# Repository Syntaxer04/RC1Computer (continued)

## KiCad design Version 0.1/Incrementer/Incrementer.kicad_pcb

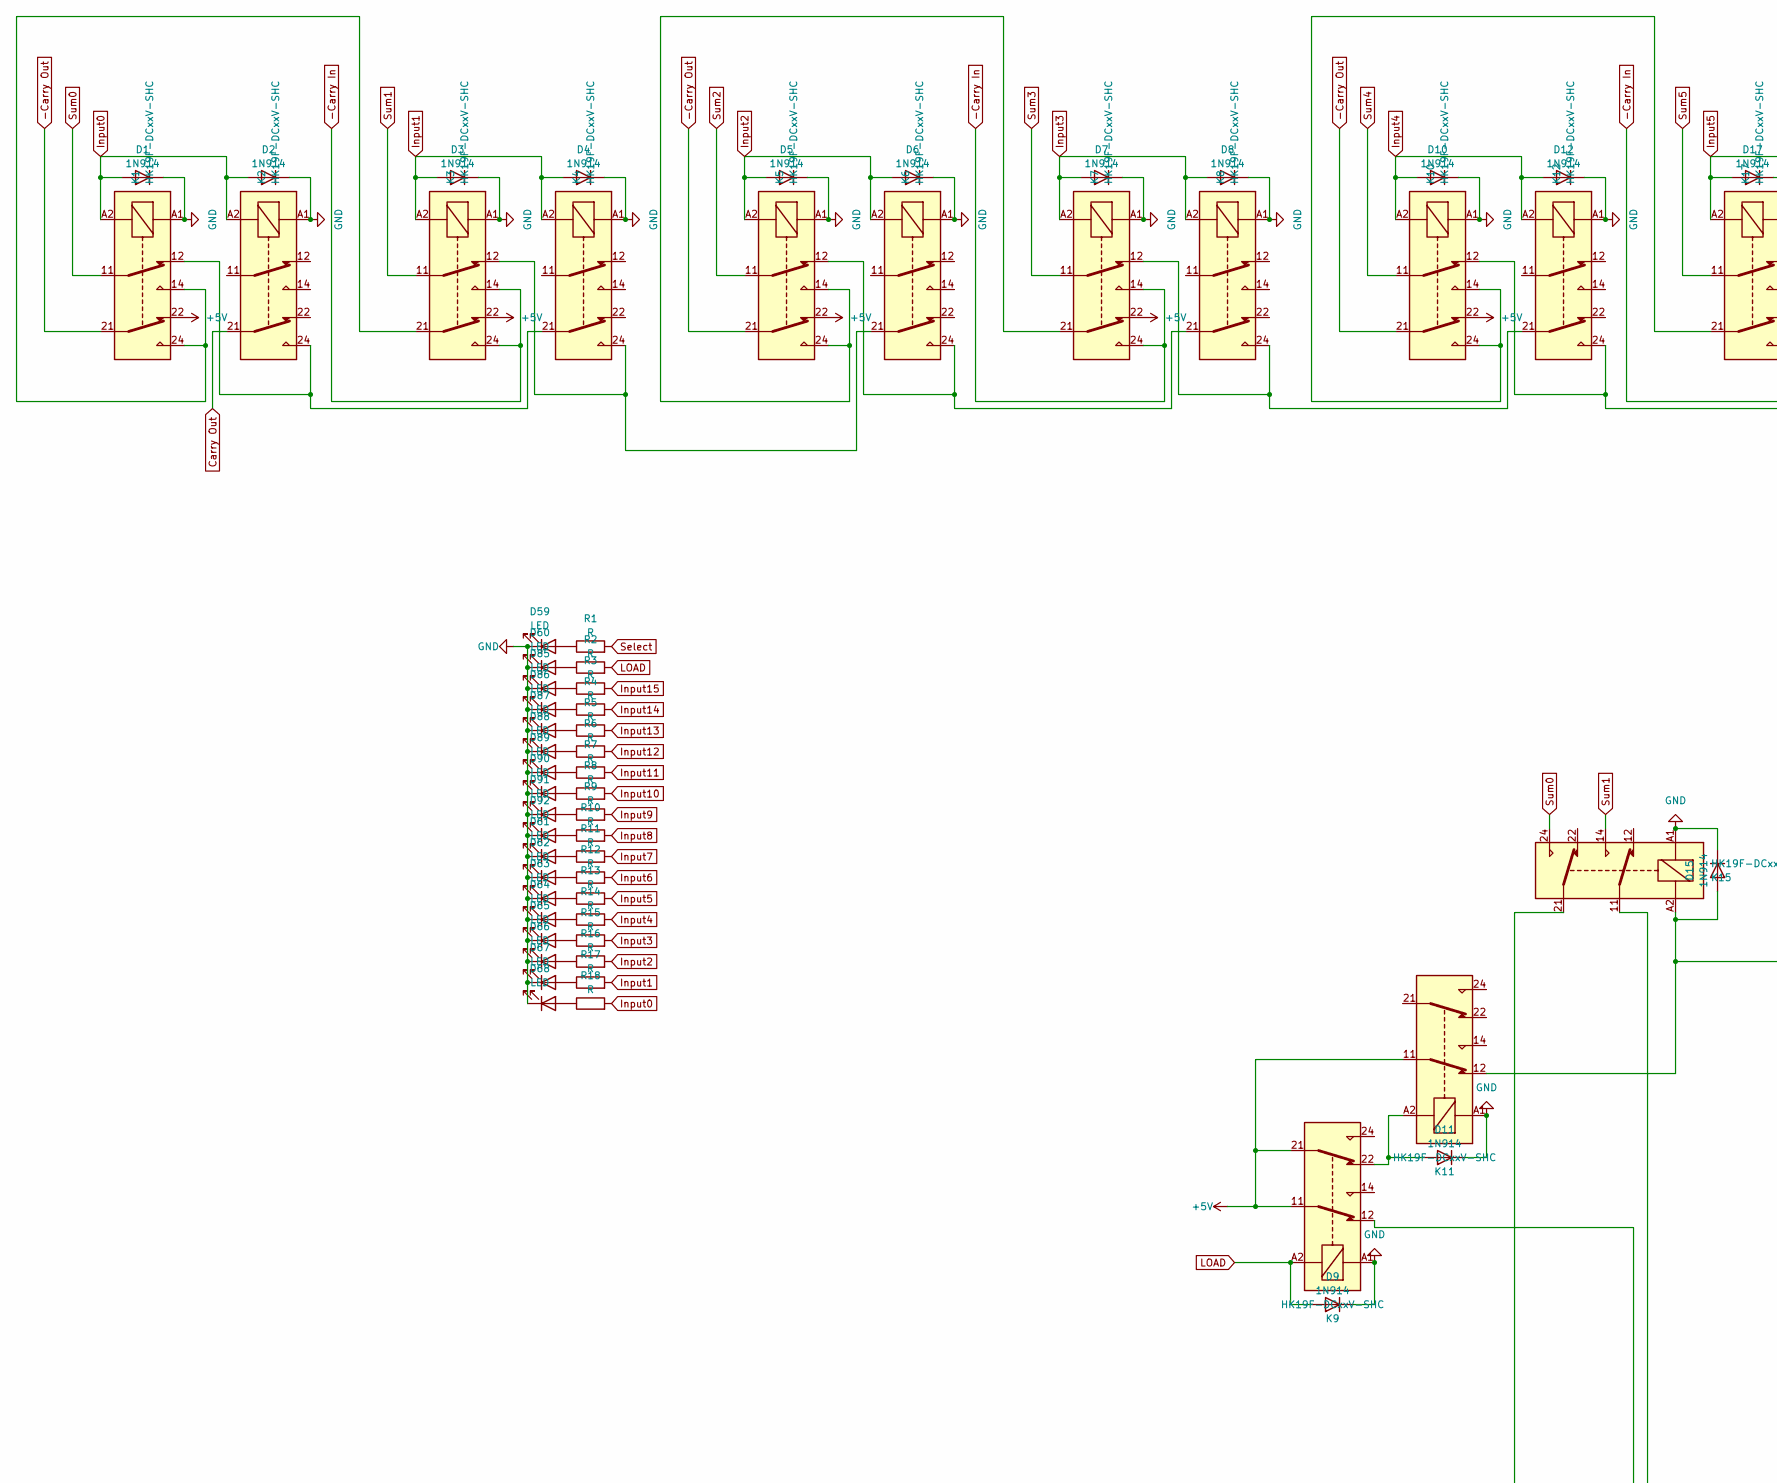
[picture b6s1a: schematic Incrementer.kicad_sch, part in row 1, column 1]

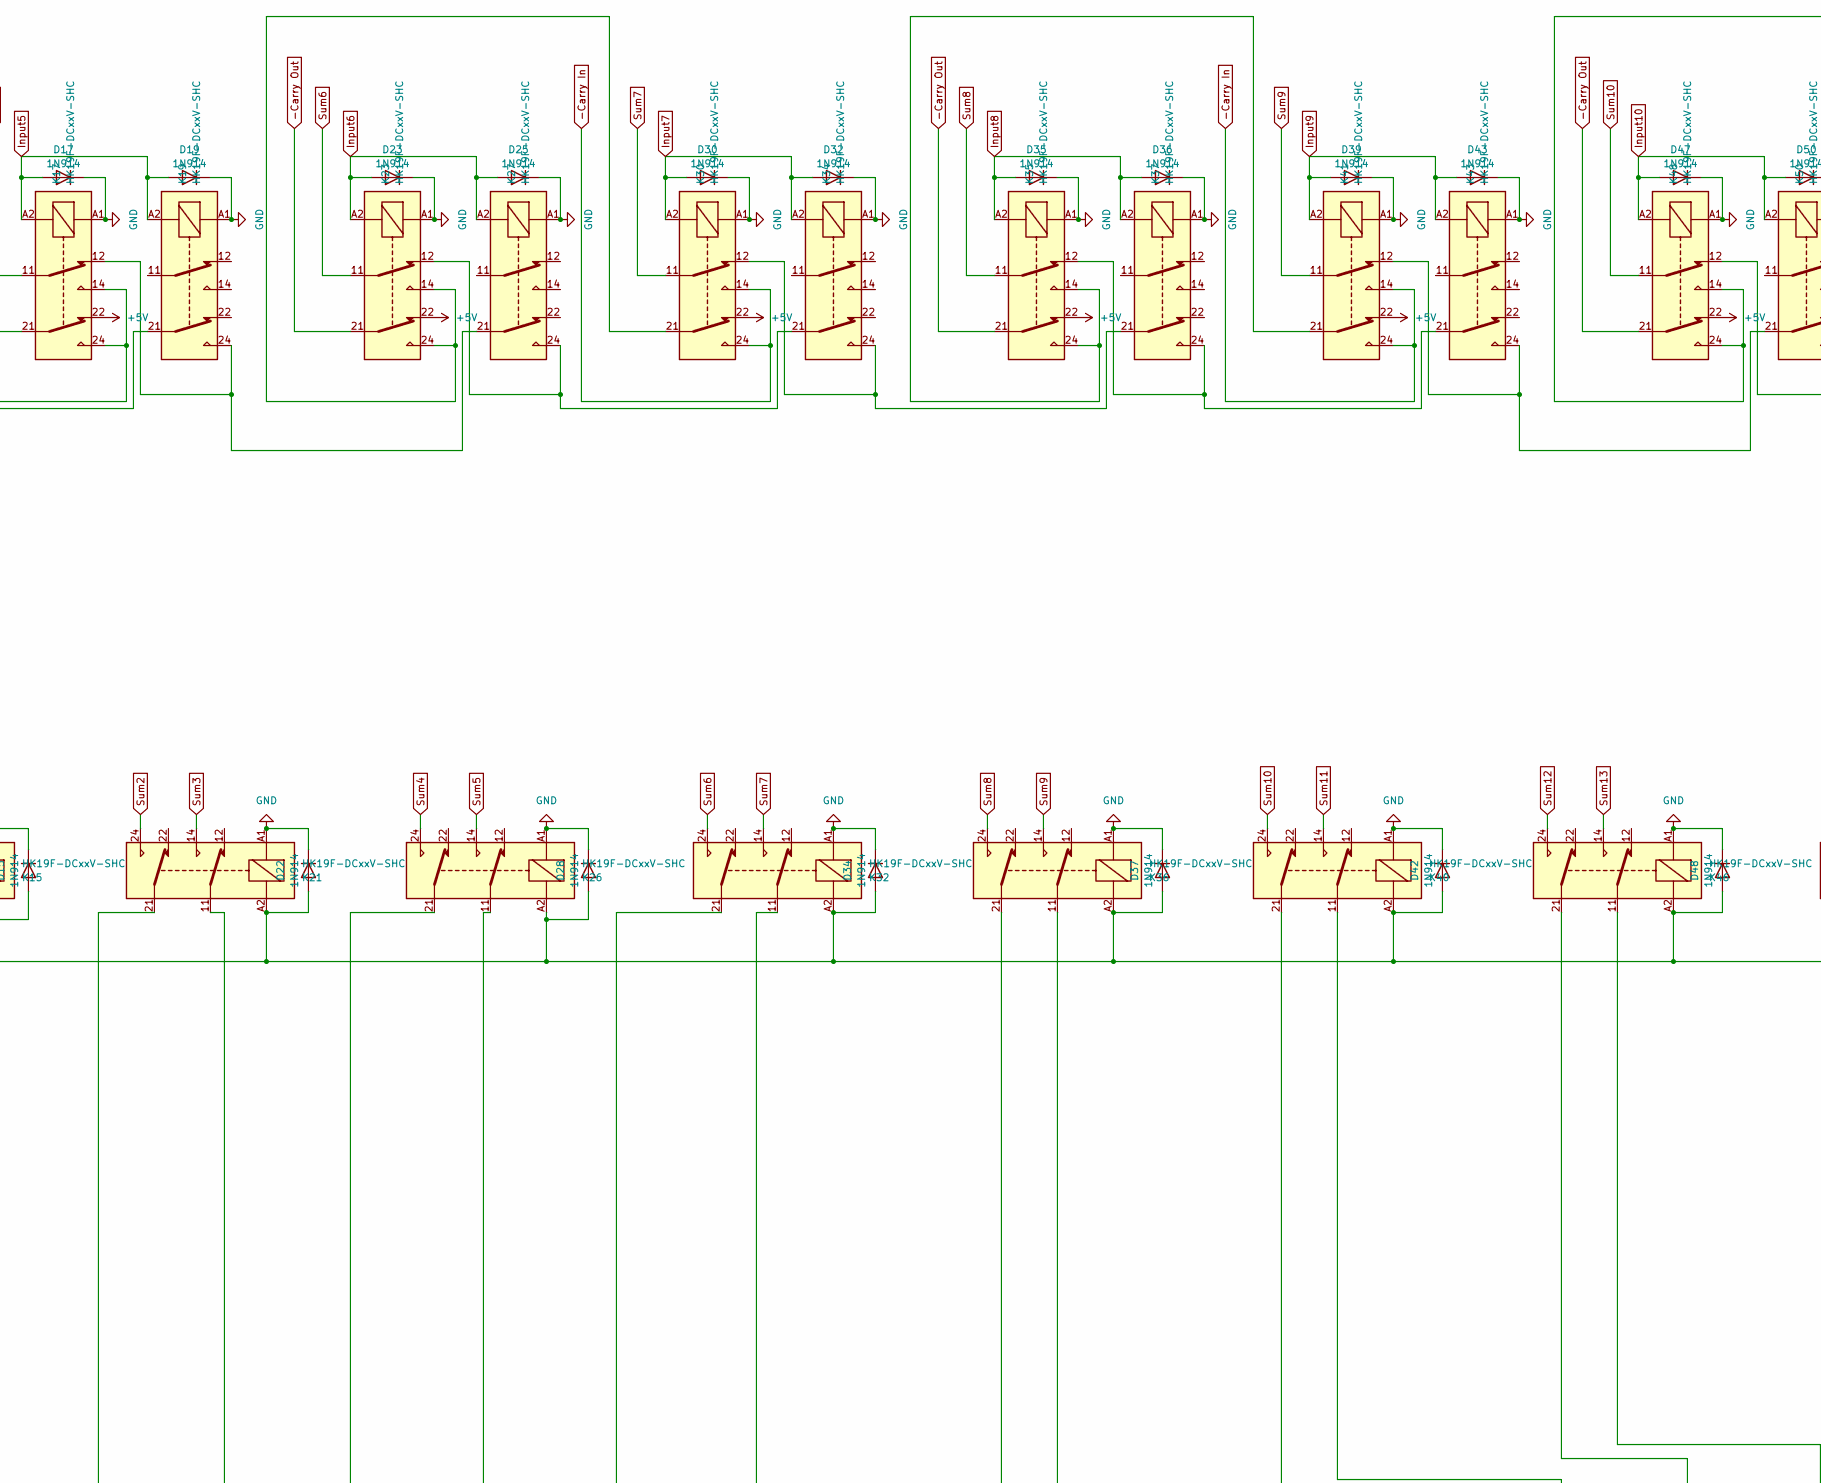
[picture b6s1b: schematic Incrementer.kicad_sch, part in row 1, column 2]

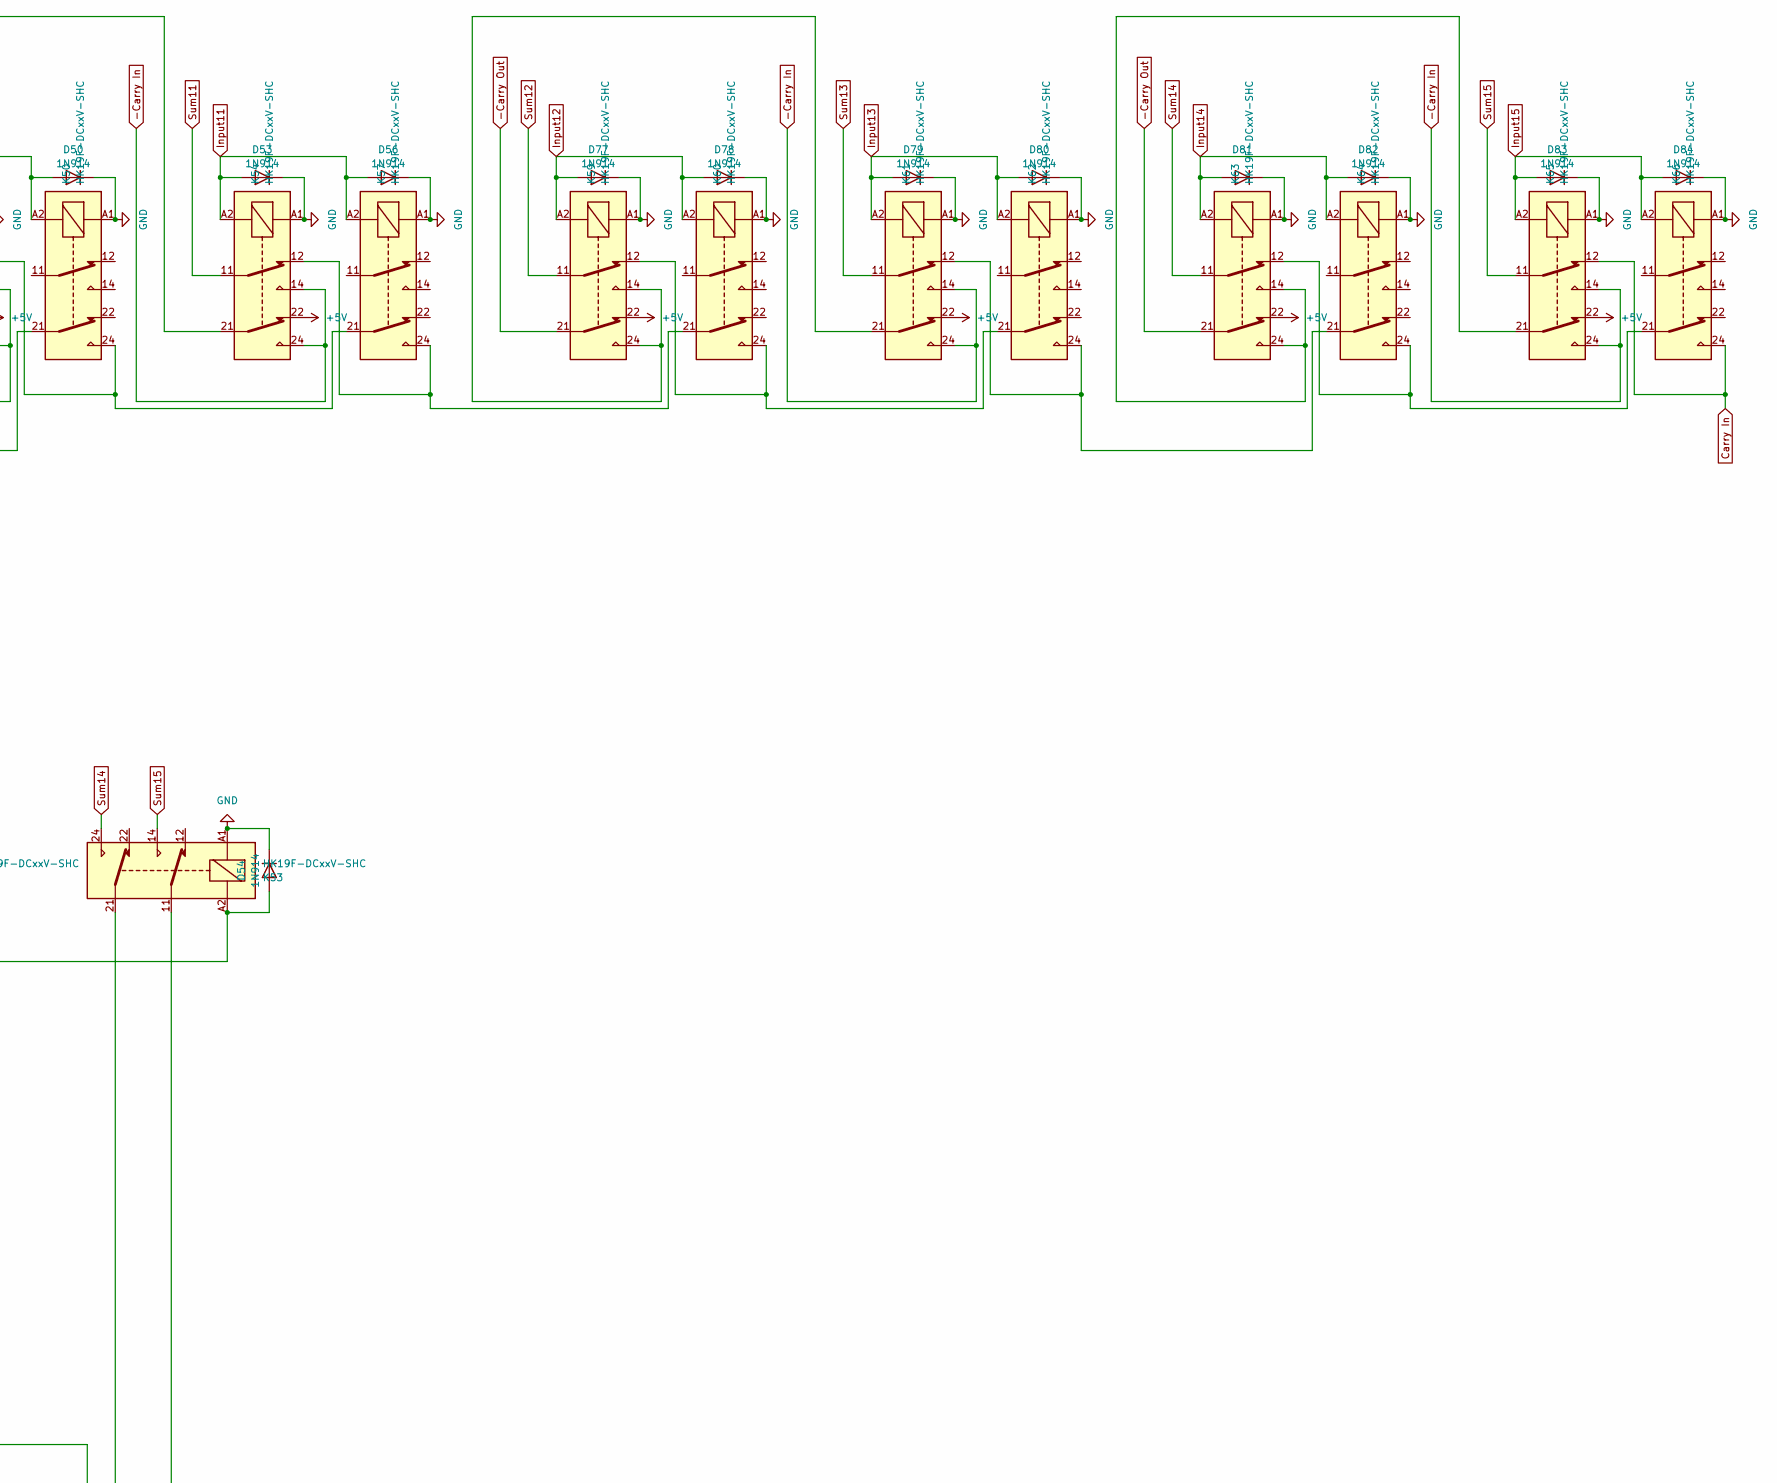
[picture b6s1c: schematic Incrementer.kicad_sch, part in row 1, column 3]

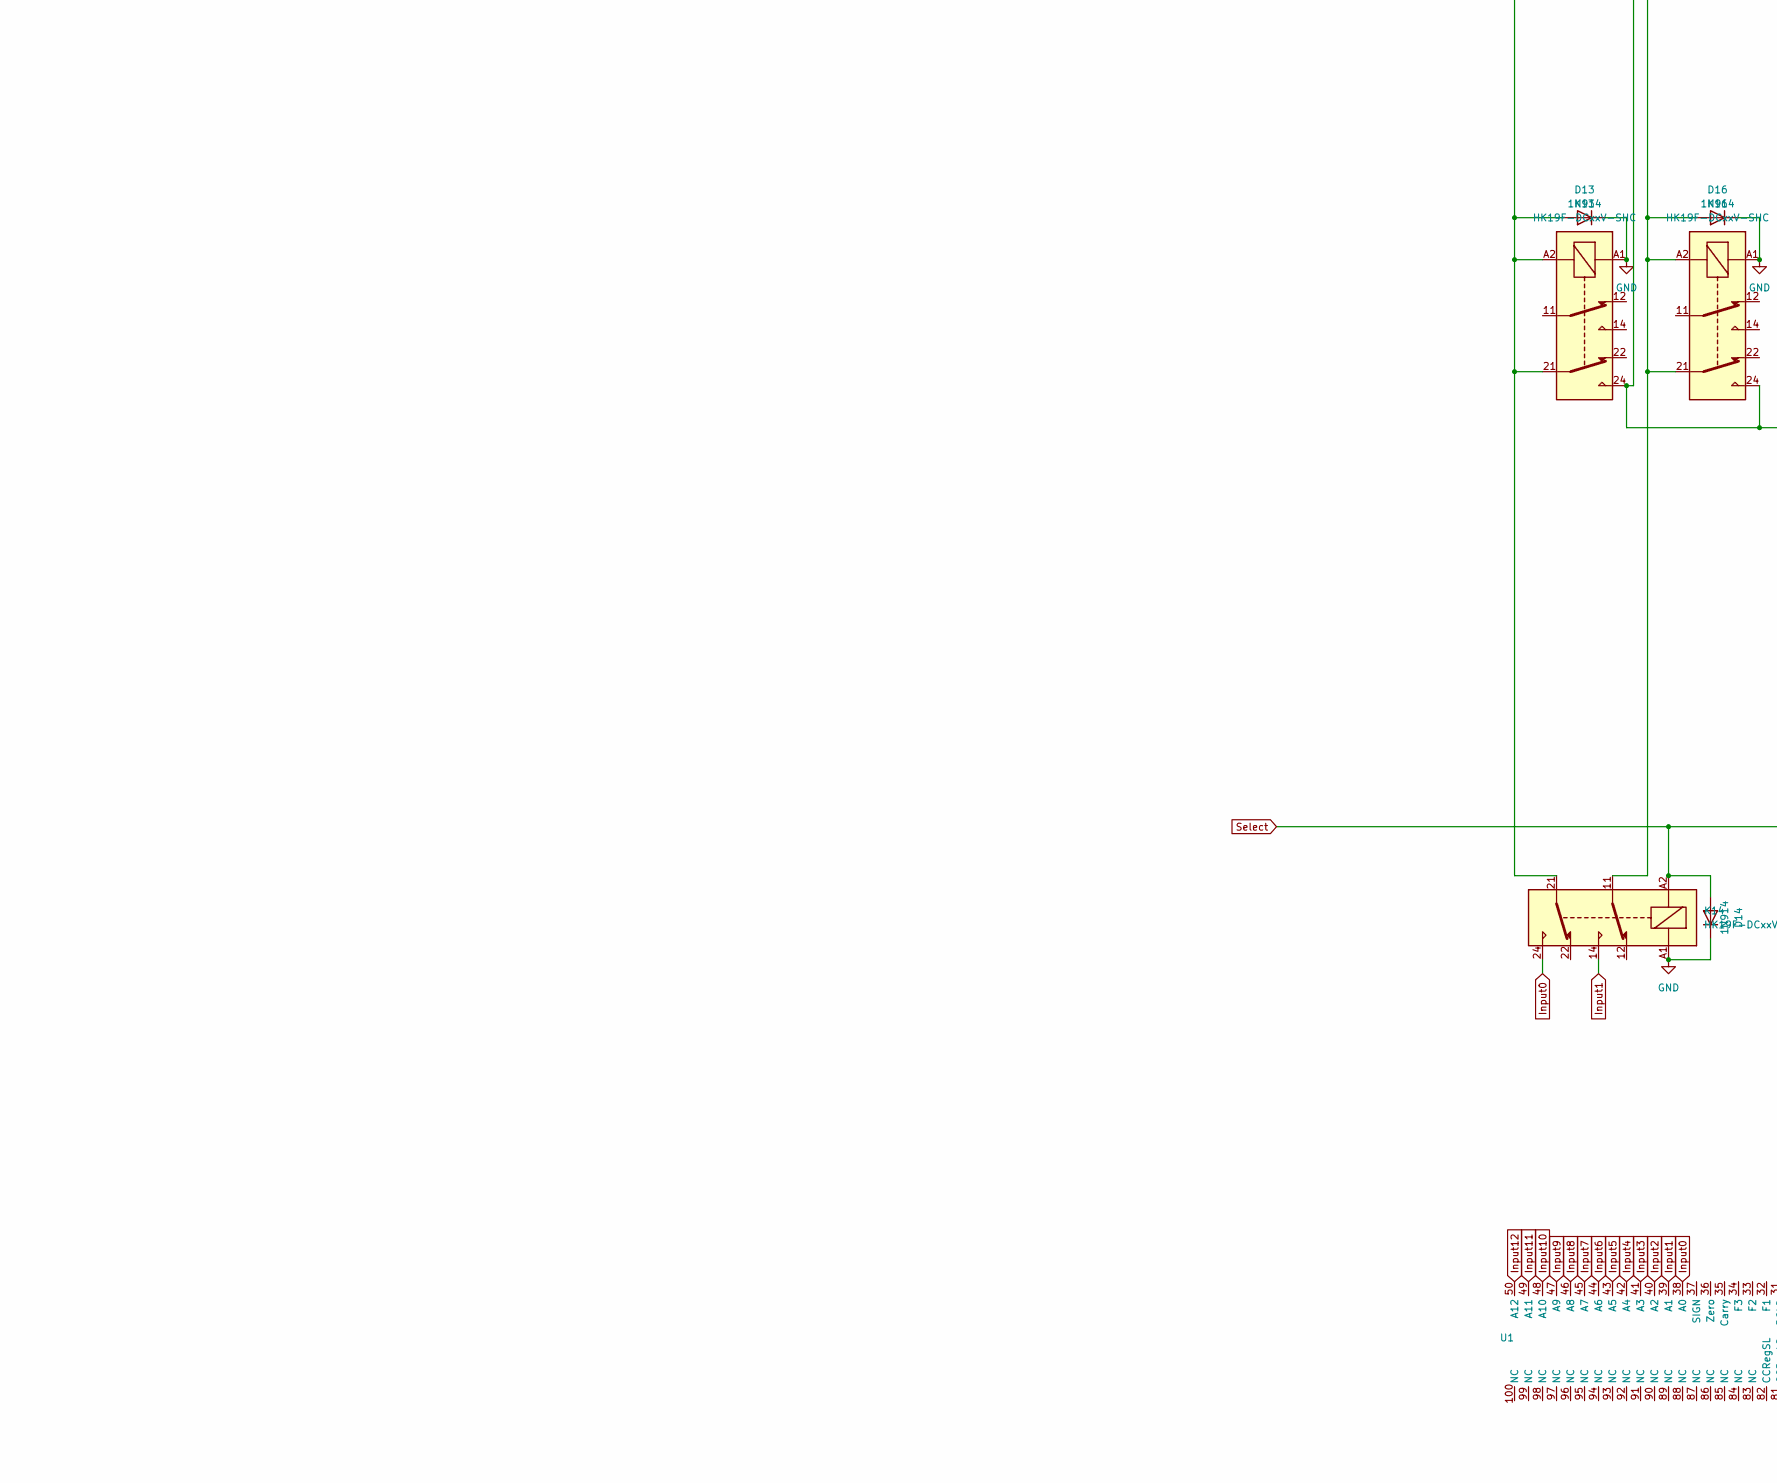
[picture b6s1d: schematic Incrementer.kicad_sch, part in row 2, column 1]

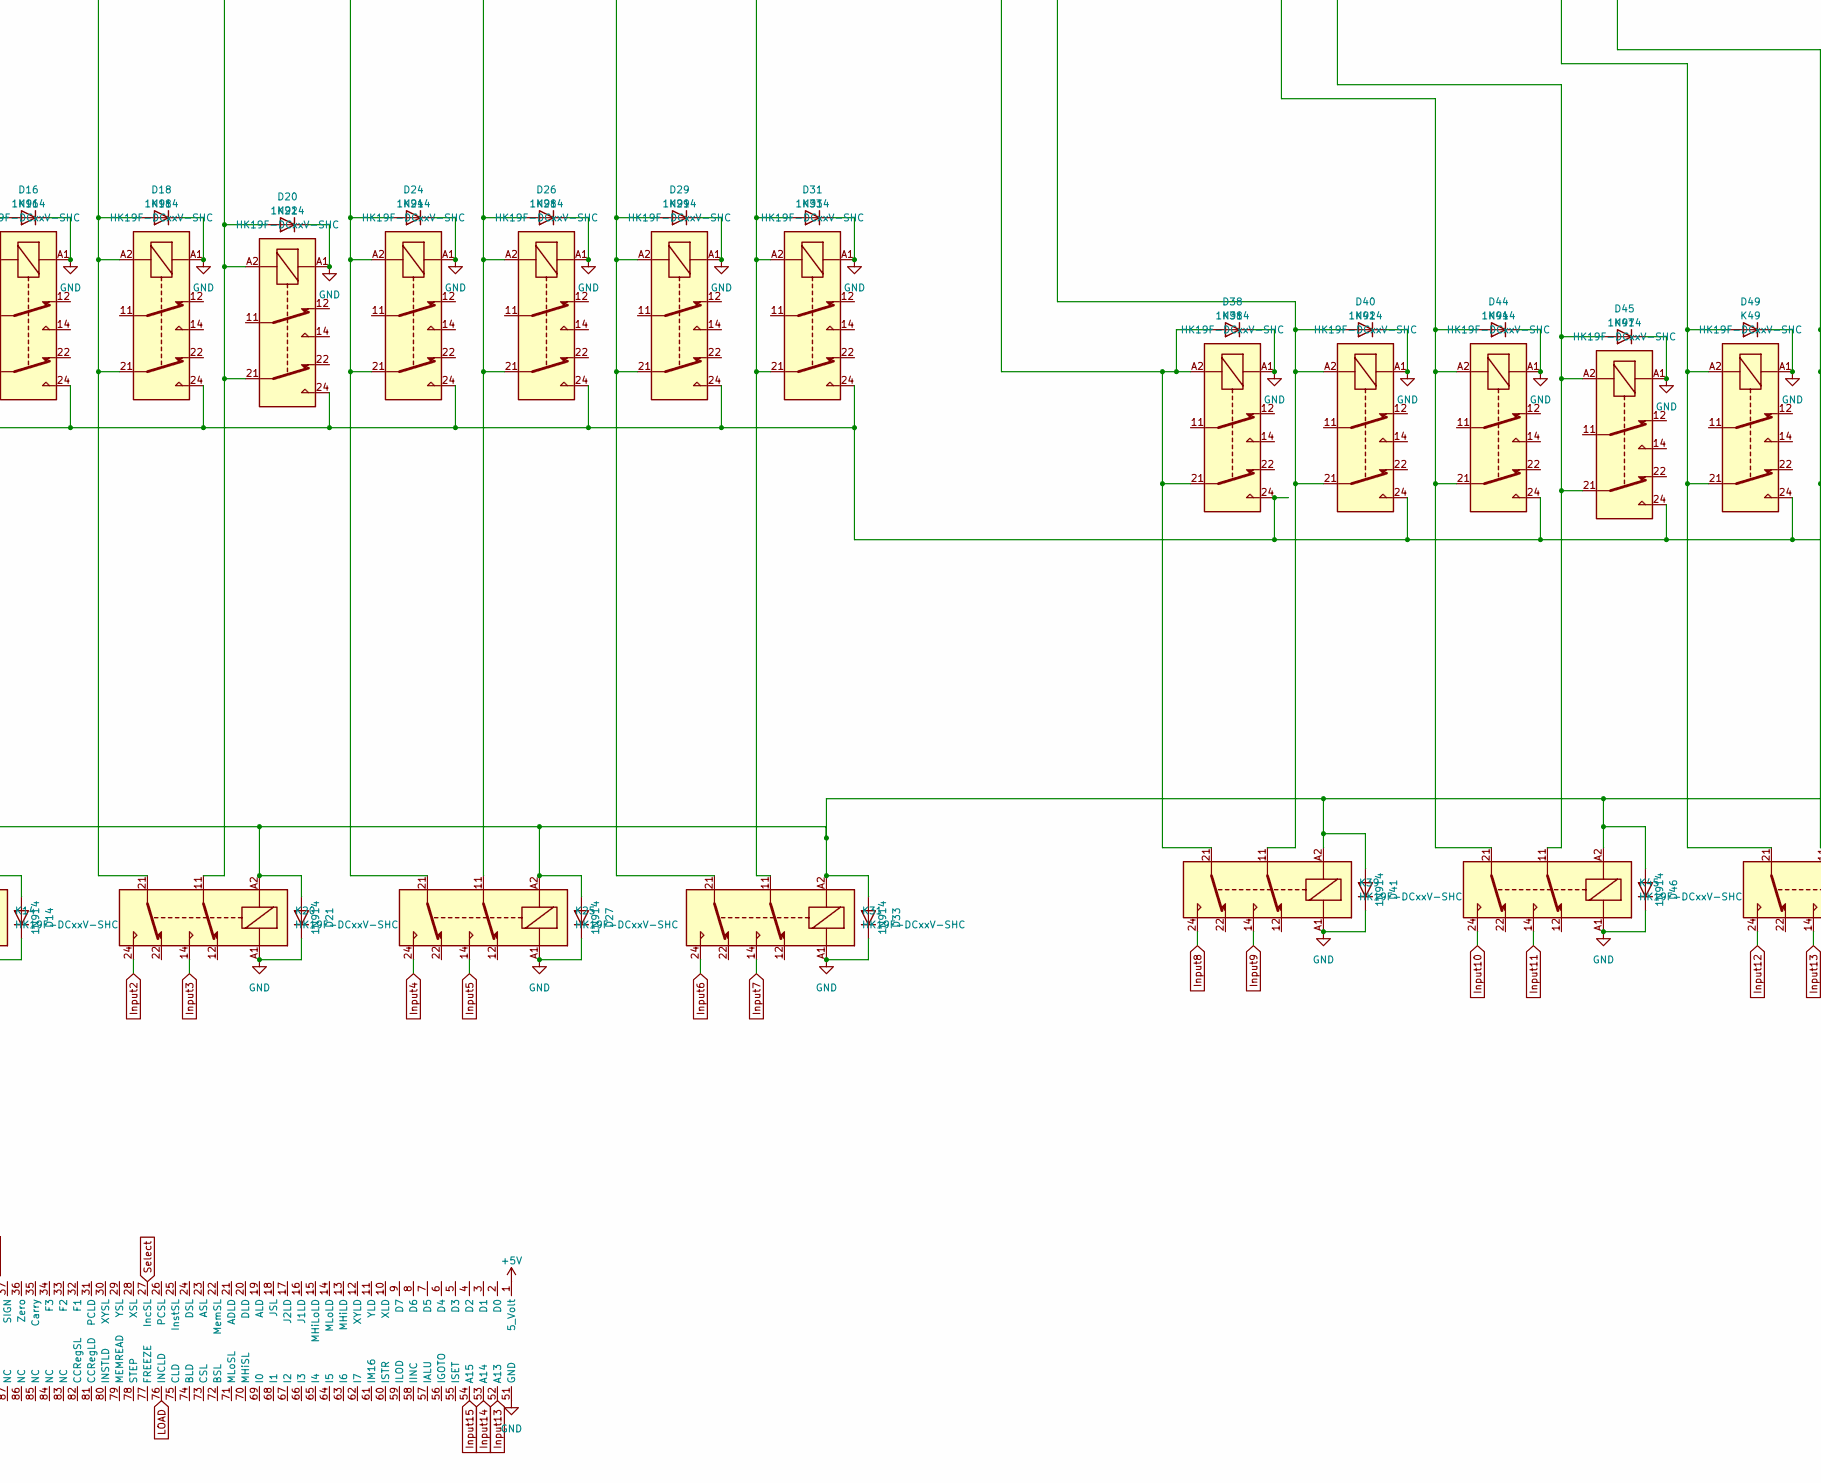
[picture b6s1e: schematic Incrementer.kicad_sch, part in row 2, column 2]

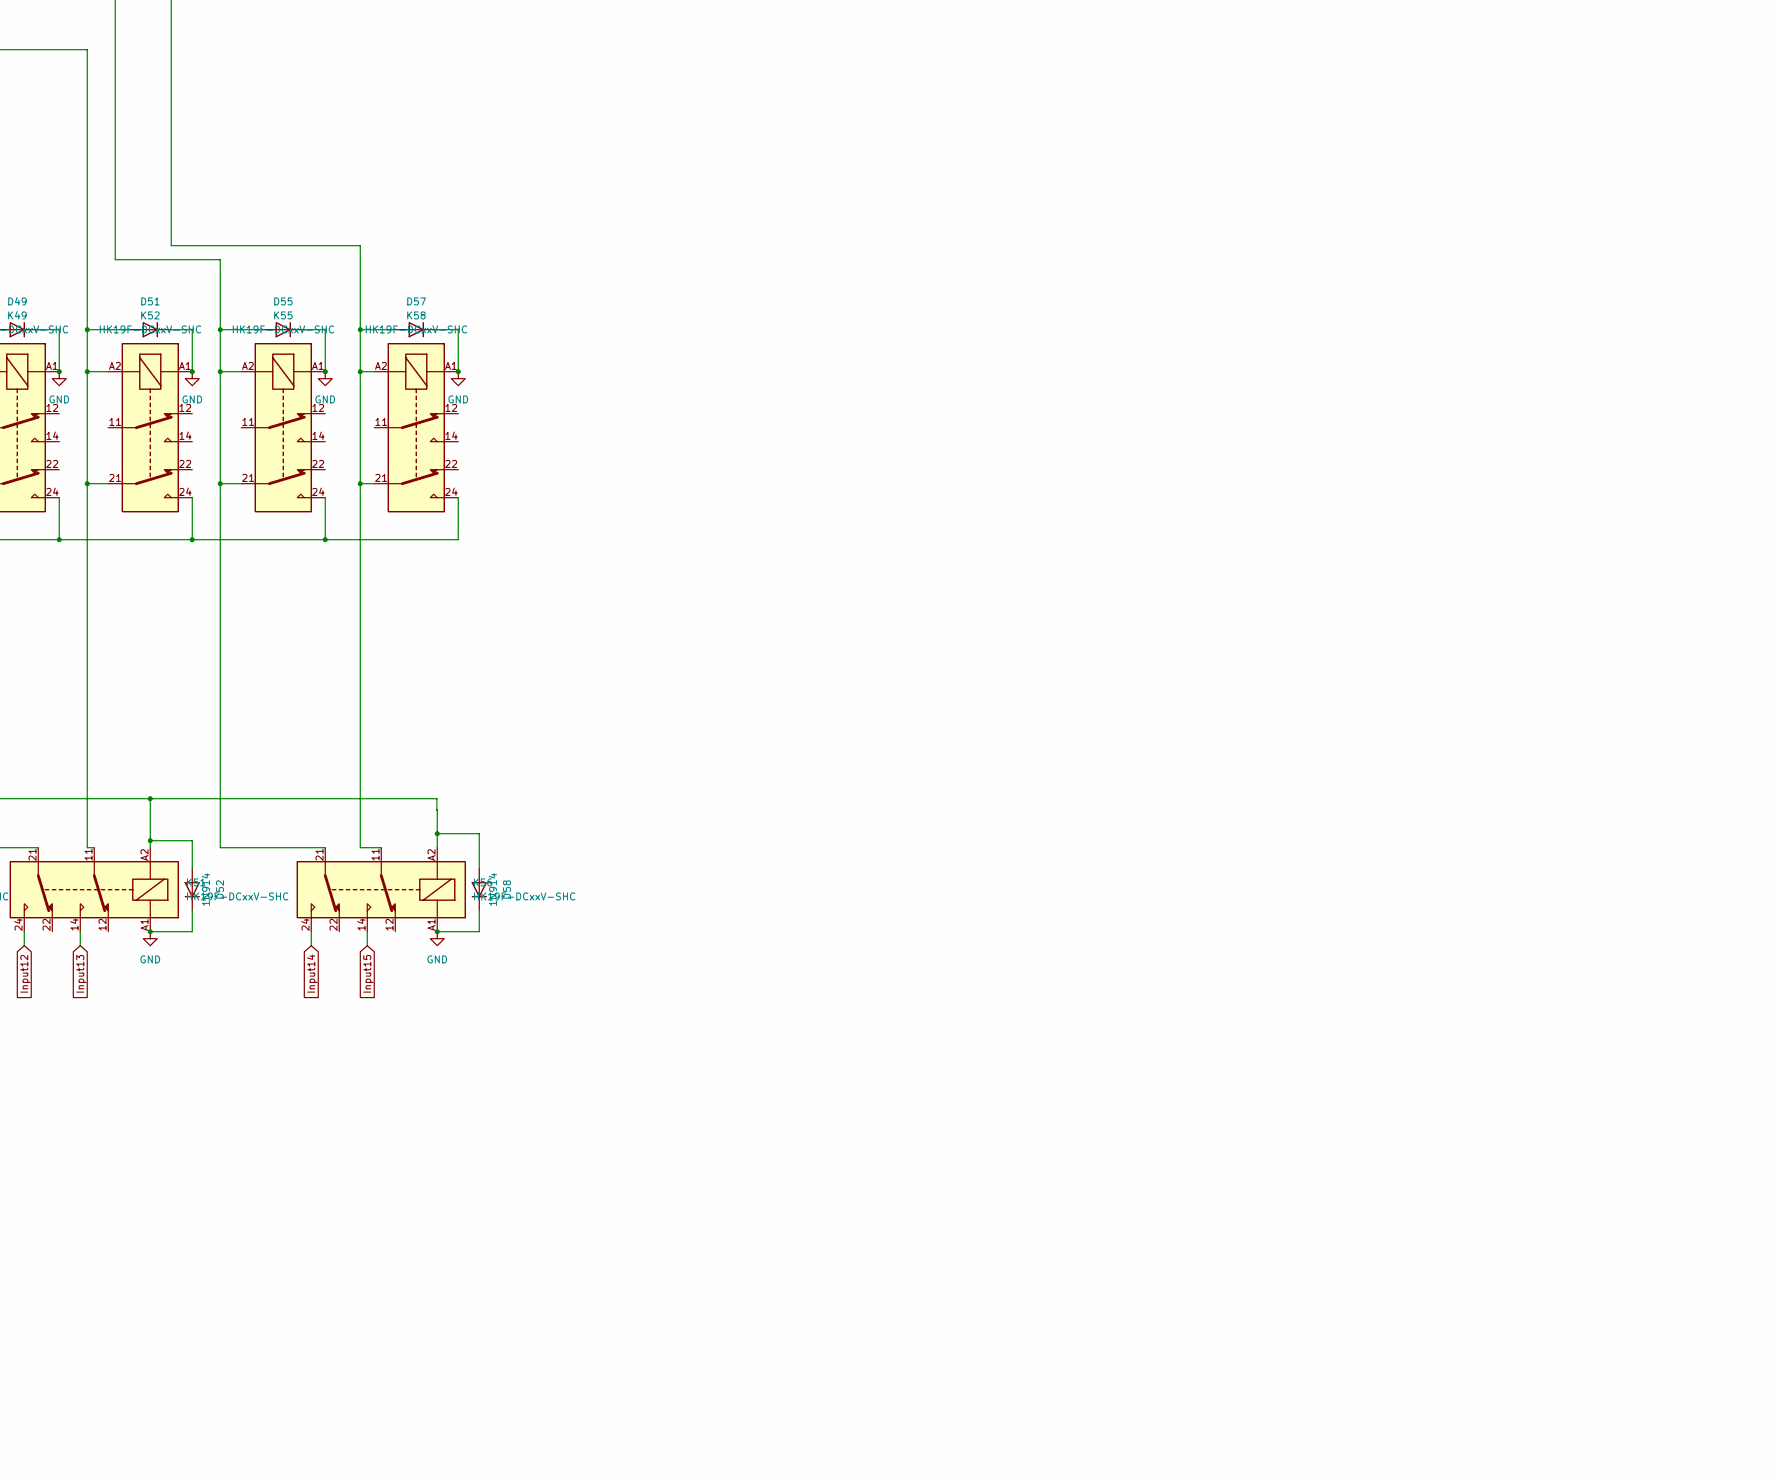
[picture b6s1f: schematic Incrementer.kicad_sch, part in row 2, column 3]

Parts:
D1, D2, D3, D4, D5, D6, D7, D8, D9, D10, D11, D12, D13, D14, D15, D16, D17, D18, D19, D20, D21, D22, D23, D24, D25, D26, D27, D28, D29, D30, D31, D32, D33, D34, D35, D36, D37, D38, D39, D40, D41, D42, D43, D44, D45, D46, D47, D48, D49, D50, D51, D52, D53, D54, D55, D56, D57, D58, D77, D78, D79, D80, D81, D82, D83, D84: 1N914; D_DO-35_SOD27_P7.62mm_Horizontal
D59, D60, D61, D62, D63, D64, D65, D66, D67, D68, D85, D86, D87, D88, D89, D90, D91, D92: LED; LED_D3.0mm
K1, K2, K3, K4, K5, K6, K7, K8, K9, K10, K11, K12, K13, K14, K15, K16, K17, K18, K19, K20, K21, K22, K23, K24, K25, K26, K27, K28, K29, K30, K31, K32, K33, K34, K35, K36, K37, K38, K39, K40, K41, K42, K43, K44, K45, K46, K47, K48, K49, K50, K51, K52, K53, K54, K55, K56, K57, K58, K59, K60, K61, K62, K63, K64, K65, K66: HK19F-DCxxV-SHC; Relay_DPDT_Finder_30.22
R1, R2, R3, R4, R5, R6, R7, R8, R9, R10, R11, R12, R13, R14, R15, R16, R17, R18: R; R_Axial_DIN0207_L6.3mm_D2.5mm_P7.62mm_Horizontal
U1: Conn_RC_Male_100

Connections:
+5V: K1.22, K3.22, K5.22, K7.22, K9.11, K9.21, K10.22, K11.11, K17.22, K23.22, K30.22, K35.22, K41.22, K48.22, K54.22, K59.22, K61.22, K63.22, K65.22, U1.1 (5_Volt)
-Carry In: K3.14, K3.24, K7.14, K7.24, K17.14, K17.24, K30.14, K30.24, K41.14, K41.24, K54.14, K54.24, K61.14, K61.24, K65.14, K65.24
-Carry Out: K1.21, K5.21, K10.21, K23.21, K35.21, K48.21, K59.21, K63.21
Carry In: K65.12, K66.24
Carry Out: K2.21
GND: D1.1 (K), D2.1 (K), D3.1 (K), D4.1 (K), D5.1 (K), D6.1 (K), D7.1 (K), D8.1 (K), D9.1 (K), D10.1 (K), D11.1 (K), D12.1 (K), D13.1 (K), D14.1 (K), D15.1 (K), D16.1 (K), D17.1 (K), D18.1 (K), D19.1 (K), D20.1 (K), D21.1 (K), D22.1 (K), D23.1 (K), D24.1 (K), D25.1 (K), D26.1 (K), D27.1 (K), D28.1 (K), D29.1 (K), D30.1 (K), D31.1 (K), D32.1 (K), D33.1 (K), D34.1 (K), D35.1 (K), D36.1 (K), D37.1 (K), D38.1 (K), D39.1 (K), D40.1 (K), D41.1 (K), D42.1 (K), D43.1 (K), D44.1 (K), D45.1 (K), D46.1 (K), D47.1 (K), D48.1 (K), D49.1 (K), D50.1 (K), D51.1 (K), D52.1 (K), D53.1 (K), D54.1 (K), D55.1 (K), D56.1 (K), D57.1 (K), D58.1 (K), D59.1 (K), D60.1 (K), D61.1 (K), D62.1 (K), D63.1 (K), D64.1 (K), D65.1 (K), D66.1 (K), D67.1 (K), D68.1 (K), D77.1 (K), D78.1 (K), D79.1 (K), D80.1 (K), D81.1 (K), D82.1 (K), D83.1 (K), D84.1 (K), D85.1 (K), D86.1 (K), D87.1 (K), D88.1 (K), D89.1 (K), D90.1 (K), D91.1 (K), D92.1 (K), K1.A1, K2.A1, K3.A1, K4.A1, K5.A1, K6.A1, K7.A1, K8.A1, K9.A1, K10.A1, K11.A1, K12.A1, K13.A1, K14.A1, K15.A1, K16.A1, K17.A1, K18.A1, K19.A1, K20.A1, K21.A1, K22.A1, K23.A1, K24.A1, K25.A1, K26.A1, K27.A1, K28.A1, K29.A1, K30.A1, K31.A1, K32.A1, K33.A1, K34.A1, K35.A1, K36.A1, K37.A1, K38.A1, K39.A1, K40.A1, K41.A1, K42.A1, K43.A1, K44.A1, K45.A1, K46.A1, K47.A1, K48.A1, K49.A1, K50.A1, K51.A1, K52.A1, K53.A1, K54.A1, K55.A1, K56.A1, K57.A1, K58.A1, K59.A1, K60.A1, K61.A1, K62.A1, K63.A1, K64.A1, K65.A1, K66.A1, U1.51 (GND)
Input0: D1.2 (A), D2.2 (A), K1.A2, K2.A2, K14.24, R18.2, U1.38 (A0)
Input1: D3.2 (A), D4.2 (A), K3.A2, K4.A2, K14.14, R17.2, U1.39 (A1)
Input2: D5.2 (A), D6.2 (A), K5.A2, K6.A2, K20.24, R16.2, U1.40 (A2)
Input3: D7.2 (A), D8.2 (A), K7.A2, K8.A2, K20.14, R15.2, U1.41 (A3)
Input4: D10.2 (A), D12.2 (A), K10.A2, K12.A2, K25.24, R14.2, U1.42 (A4)
Input5: D17.2 (A), D19.2 (A), K17.A2, K19.A2, K25.14, R13.2, U1.43 (A5)
Input6: D23.2 (A), D25.2 (A), K23.A2, K27.A2, K31.24, R12.2, U1.44 (A6)
Input7: D30.2 (A), D32.2 (A), K30.A2, K31.14, K34.A2, R11.2, U1.45 (A7)
Input8: D35.2 (A), D36.2 (A), K35.A2, K37.A2, K39.24, R10.2, U1.46 (A8)
Input9: D39.2 (A), D43.2 (A), K39.14, K41.A2, K43.A2, R9.2, U1.47 (A9)
Input10: D47.2 (A), D50.2 (A), K45.24, K48.A2, K50.A2, R8.2, U1.48 (A10)
Input11: D53.2 (A), D56.2 (A), K45.14, K54.A2, K57.A2, R7.2, U1.49 (A11)
Input12: D77.2 (A), D78.2 (A), K51.24, K59.A2, K60.A2, R6.2, U1.50 (A12)
Input13: D79.2 (A), D80.2 (A), K51.14, K61.A2, K62.A2, R5.2, U1.52 (A13)
Input14: D81.2 (A), D82.2 (A), K56.24, K63.A2, K64.A2, R4.2, U1.53 (A14)
Input15: D83.2 (A), D84.2 (A), K56.14, K65.A2, K66.A2, R3.2, U1.54 (A15)
LOAD: D9.2 (A), K9.A2, R2.2, U1.76 (INCLD)
unnamed: D11.2 (A), K9.22, K11.A2
unnamed: D13.2 (A), K13.21, K13.A2, K14.21, K15.21
unnamed: D15.2 (A), D22.2 (A), D28.2 (A), D34.2 (A), D37.2 (A), D42.2 (A), D48.2 (A), D54.2 (A), K11.12, K15.A2, K21.A2, K26.A2, K32.A2, K36.A2, K40.A2, K46.A2, K53.A2
unnamed: D16.2 (A), K14.11, K15.11, K16.21, K16.A2
unnamed: D18.2 (A), K18.21, K18.A2, K20.21, K21.21
unnamed: D20.2 (A), K20.11, K21.11, K22.21, K22.A2
unnamed: D24.2 (A), K24.21, K24.A2, K25.21, K26.21
unnamed: D26.2 (A), K25.11, K26.11, K28.21, K28.A2
unnamed: D29.2 (A), K29.21, K29.A2, K31.21, K32.21
unnamed: D31.2 (A), K31.11, K32.11, K33.21, K33.A2
unnamed: D38.2 (A), K36.21, K38.21, K38.A2, K39.21
unnamed: D40.2 (A), K36.11, K39.11, K42.21, K42.A2
unnamed: D44.2 (A), K40.21, K44.21, K44.A2, K45.21
unnamed: D45.2 (A), K40.11, K45.11, K47.21, K47.A2
unnamed: D49.2 (A), K46.21, K49.21, K49.A2, K51.21
unnamed: D51.2 (A), K46.11, K51.11, K52.21, K52.A2
unnamed: D55.2 (A), K53.21, K55.21, K55.A2, K56.21
unnamed: D57.2 (A), K53.11, K56.11, K58.21, K58.A2
unnamed: D59.2 (A), R1.1
unnamed: D60.2 (A), R2.1
unnamed: D61.2 (A), R11.1
unnamed: D62.2 (A), R12.1
unnamed: D63.2 (A), R13.1
unnamed: D64.2 (A), R14.1
unnamed: D65.2 (A), R15.1
unnamed: D66.2 (A), R16.1
unnamed: D67.2 (A), R17.1
unnamed: D68.2 (A), R18.1
unnamed: D85.2 (A), R3.1
unnamed: D86.2 (A), R4.1
unnamed: D87.2 (A), R5.1
unnamed: D88.2 (A), R6.1
unnamed: D89.2 (A), R7.1
unnamed: D90.2 (A), R8.1
unnamed: D91.2 (A), R9.1
unnamed: D92.2 (A), R10.1
unnamed: K1.12, K2.24, K4.21
unnamed: K1.14, K1.24, K3.21
unnamed: K3.12, K4.24, K6.21
unnamed: K5.12, K6.24, K8.21
unnamed: K5.14, K5.24, K7.21
unnamed: K10.12, K12.24, K19.21
unnamed: K10.14, K10.24, K17.21
unnamed: K7.12, K8.24, K12.21
unnamed: K9.12, K13.24, K16.24, K18.24, K22.24, K24.24, K28.24, K29.24, K33.24, K38.24, K42.24, K44.24, K47.24, K49.24, K52.24, K55.24, K58.24
unnamed: K17.12, K19.24, K27.21
unnamed: K23.12, K27.24, K34.21
unnamed: K23.14, K23.24, K30.21
unnamed: K30.12, K34.24, K37.21
unnamed: K35.12, K37.24, K43.21
unnamed: K35.14, K35.24, K41.21
unnamed: K41.12, K43.24, K50.21
unnamed: K48.12, K50.24, K57.21
unnamed: K48.14, K48.24, K54.21
unnamed: K54.12, K57.24, K60.21
unnamed: K59.12, K60.24, K62.21
unnamed: K59.14, K59.24, K61.21
unnamed: K61.12, K62.24, K64.21
unnamed: K63.12, K64.24, K66.21
unnamed: K63.14, K63.24, K65.21
Select: D14.2 (A), D21.2 (A), D27.2 (A), D33.2 (A), D41.2 (A), D46.2 (A), D52.2 (A), D58.2 (A), K14.A2, K20.A2, K25.A2, K31.A2, K39.A2, K45.A2, K51.A2, K56.A2, R1.2, U1.27 (IncSL)
Sum0: K1.11, K15.24
Sum1: K3.11, K15.14
Sum2: K5.11, K21.24
Sum3: K7.11, K21.14
Sum4: K10.11, K26.24
Sum5: K17.11, K26.14
Sum6: K23.11, K32.24
Sum7: K30.11, K32.14
Sum8: K35.11, K36.24
Sum9: K36.14, K41.11
Sum10: K40.24, K48.11
Sum11: K40.14, K54.11
Sum12: K46.24, K59.11
Sum13: K46.14, K61.11
Sum14: K53.24, K63.11
Sum15: K53.14, K65.11

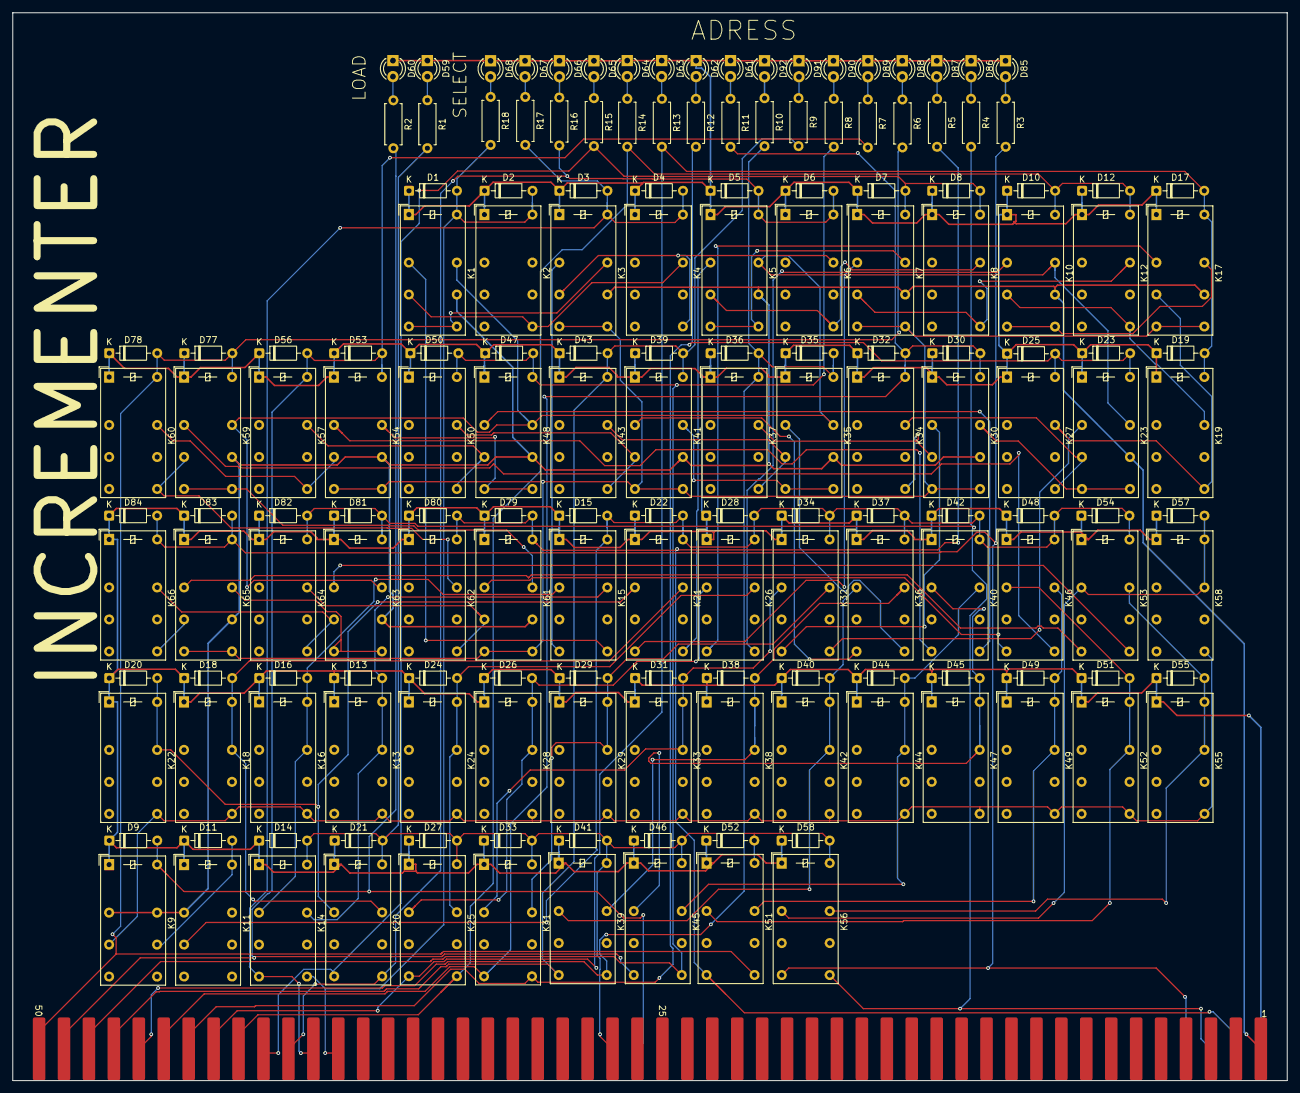
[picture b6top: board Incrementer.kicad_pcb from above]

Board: 2 copper layers, 202.4 x 169.6 mm, 169 parts (0 on the bottom side), 99 nets.
